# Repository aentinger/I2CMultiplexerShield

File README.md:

💾 I2C Multiplexer Shield
=========================

# 📸 Image

# 📂 Description

Originally many I2C slave devices as temperature sensors, distance sensors, RAM/ROM, digital I/O expanders had only a single I2C address. As a consequence, only one such I2C slave could be operated on one I2C. If one wanted to operate multiple I2C slaves with identical address, multiple I2C buses with its own I2C master were necessary. To overcome this limitation, modern I2C slaves have a base address, which can be varied by setting of '0' and '1' on special address pins. Thereby, typically between 4 and 8 different addresses are required per I2C slave. But if onw would want to use more than the addresses offered by the I2C slave device, so again several I2C buses with its own I2C master are necessary.

The LXRobotics I2C Multiplexer Shield solves this problem by allowing the user to switch back and forth between 8 different I2C bus systems. The I2C Multiplexer Shield acts also as a level converter, so that 3,3 V I2C sensors can easily interact with the Arduino. For the quick start, a finished Arduino Library with sample programs is available

**Features**

* Control nearly any number of (similar) sensors over a single I2C bus
* Multiplexing of 8 different I2C buses on 1 I2C bus
* I2C-Pullups via Jumper shiftable
* Selection of the I2C bus voltage between 5 V and 3,3 V via jumper possible (optionally, can be also fed any arbitrary I2C bus voltage)
* Up to 8 different I2C addresses of the I2C Multiplexer Shields configurable via jumper
* Arduino Library available for control with example programms

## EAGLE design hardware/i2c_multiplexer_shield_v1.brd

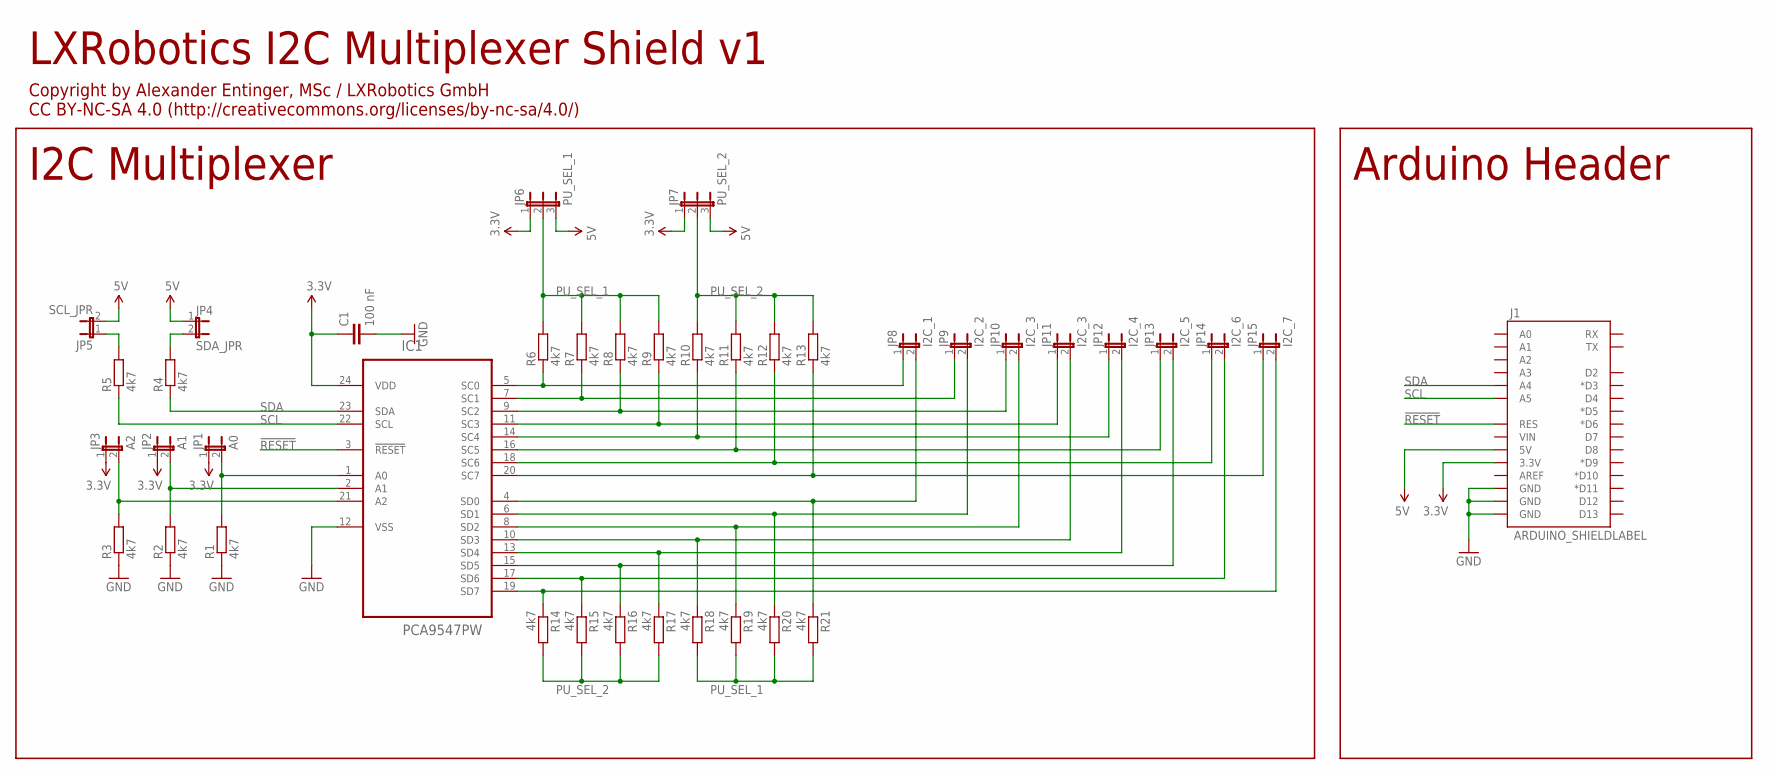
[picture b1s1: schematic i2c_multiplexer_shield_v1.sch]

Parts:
C1: 100 nF; C0805
IC1: PCA9547PW; SOP65P640X110-24N
J1: ARDUINO_SHIELDLABEL; DUEMILANOVE_SHIELD
JP1: A0; JP1
JP2: A1; JP1
JP3: A2; JP1
JP4: SDA_JPR; JP1
JP5: SCL_JPR; JP1
JP6: PU_SEL_1; JP2
JP7: PU_SEL_2; JP2
JP8: I2C_1; JP1
JP9: I2C_2; JP1
JP10, JP11: I2C_3; JP1
JP12: I2C_4; JP1
JP13: I2C_5; JP1
JP14: I2C_6; JP1
JP15: I2C_7; JP1
R1, R2, R3, R4, R5, R6, R7, R8, R9, R10, R11, R12, R13, R14, R15, R16, R17, R18, R19, R20, R21: 4k7; R0805

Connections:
3.3V: C1.1, IC1.24 (VDD), J1.3.3V, JP1.1, JP2.1, JP3.1, JP6.1, JP7.1
5V: J1.5V, JP4.1, JP5.2, JP6.3, JP7.3
!RESET: IC1.3 (!RESET), J1.RES
GND: C1.2, IC1.12 (VSS), J1.GND@0 (GND), J1.GND@1 (GND), J1.GND@2 (GND), R1.1, R2.1, R3.1
unnamed: IC1.1 (A0), JP1.2, R1.2
unnamed: IC1.2 (A1), JP2.2, R2.2
unnamed: IC1.21 (A2), JP3.2, R3.2
unnamed: JP5.1, R5.2
unnamed: JP4.2, R4.2
unnamed: IC1.5 (SC0), JP8.1, R6.1
unnamed: IC1.7 (SC1), JP9.1, R7.1
unnamed: IC1.9 (SC2), JP10.1, R8.1
unnamed: IC1.11 (SC3), JP11.1, R9.1
unnamed: IC1.14 (SC4), JP12.1, R10.1
unnamed: IC1.16 (SC5), JP13.1, R11.1
unnamed: IC1.18 (SC6), JP14.1, R12.1
unnamed: IC1.20 (SC7), JP15.1, R13.1
unnamed: IC1.4 (SD0), JP8.2, R21.1
unnamed: IC1.6 (SD1), JP9.2, R20.1
unnamed: IC1.8 (SD2), JP10.2, R19.1
unnamed: IC1.10 (SD3), JP11.2, R18.1
unnamed: IC1.13 (SD4), JP12.2, R17.1
unnamed: IC1.15 (SD5), JP13.2, R16.1
unnamed: IC1.17 (SD6), JP14.2, R15.1
unnamed: IC1.19 (SD7), JP15.2, R14.1
PU_SEL_1: JP6.2, R6.2, R7.2, R8.2, R9.2, R18.2, R19.2, R20.2, R21.2
PU_SEL_2: JP7.2, R10.2, R11.2, R12.2, R13.2, R14.2, R15.2, R16.2, R17.2
SCL: IC1.22 (SCL), J1.A5, R5.1
SDA: IC1.23 (SDA), J1.A4, R4.1

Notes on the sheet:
I2C Multiplexer
Arduino Header
LXRobotics I2C Multiplexer Shield v1
Copyright by Alexander Entinger, MSc / LXRobotics GmbH CC BY-NC-SA 4.0 (http://creativecommons.org/licenses/by-nc-sa/4.0/)

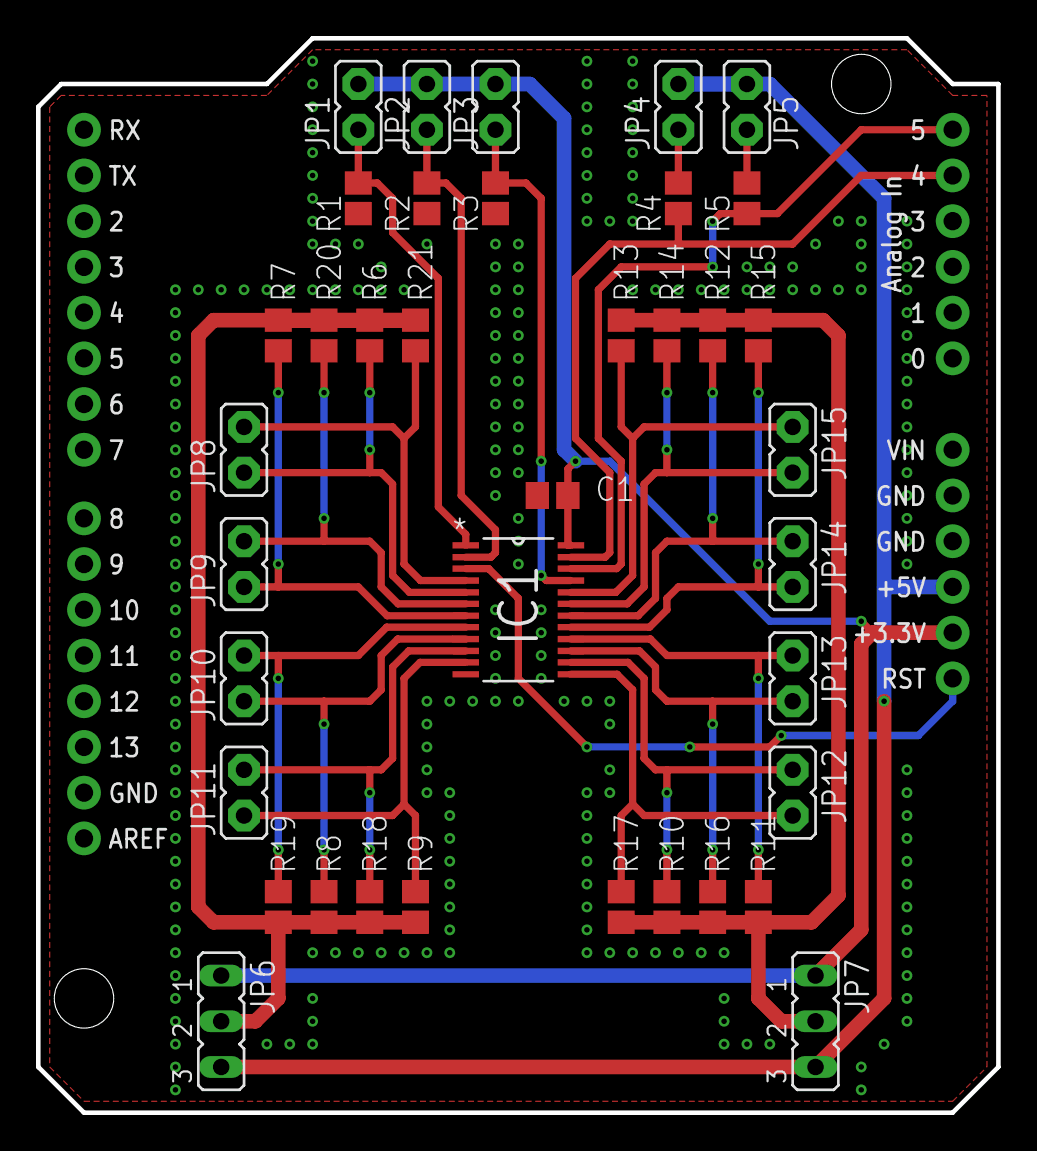
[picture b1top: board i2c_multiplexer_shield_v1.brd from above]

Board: 2 copper layers, 53.3 x 59.7 mm, 39 parts (0 on the bottom side), 29 nets.

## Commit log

2015-07-14 initial checkin of multiplexer i2c shield
2015-07-14 checkin in software library for i2c multiplexer shield
2017-06-27 Adding hardware + images
2025-03-26 Pretty up README.
2025-03-26 Upload BOM.
2025-03-26 Use relative link.

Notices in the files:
README.md:
License: CC BY-NC-SA 4.0
parts and their libraries:
SparkFun-Boards: Licensing: CC v3.0 Share-Alike You are welcome to use this library for commercial purposes.
